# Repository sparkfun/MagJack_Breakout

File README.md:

SparkFun RJ45 MagJack Breakout
================================

[*SparkFun RJ45 MagJack Breakout(BOB-13021)*](https://www.sparkfun.com/products/13021)

This is the SparkFun RJ45 MagJack Breakout, a simple board that will provide you with a way to put an ethernet port into your breadboard. 

Repository Contents
-------------------
* **/Fritzing** - Fritzing Example wiring images
* **/Hardware** - All Eagle design files (.brd, .sch)
* **/Production** - Test bed files and production panel files

License Information
-------------------
The hardware is released under [Creative Commons ShareAlike 4.0 International](https://creativecommons.org/licenses/by-sa/4.0/).
The code is beerware; if you see me (or any other SparkFun employee) at the local, and you've found our code helpful, please buy us a round!

Distributed as-is; no warranty is given.

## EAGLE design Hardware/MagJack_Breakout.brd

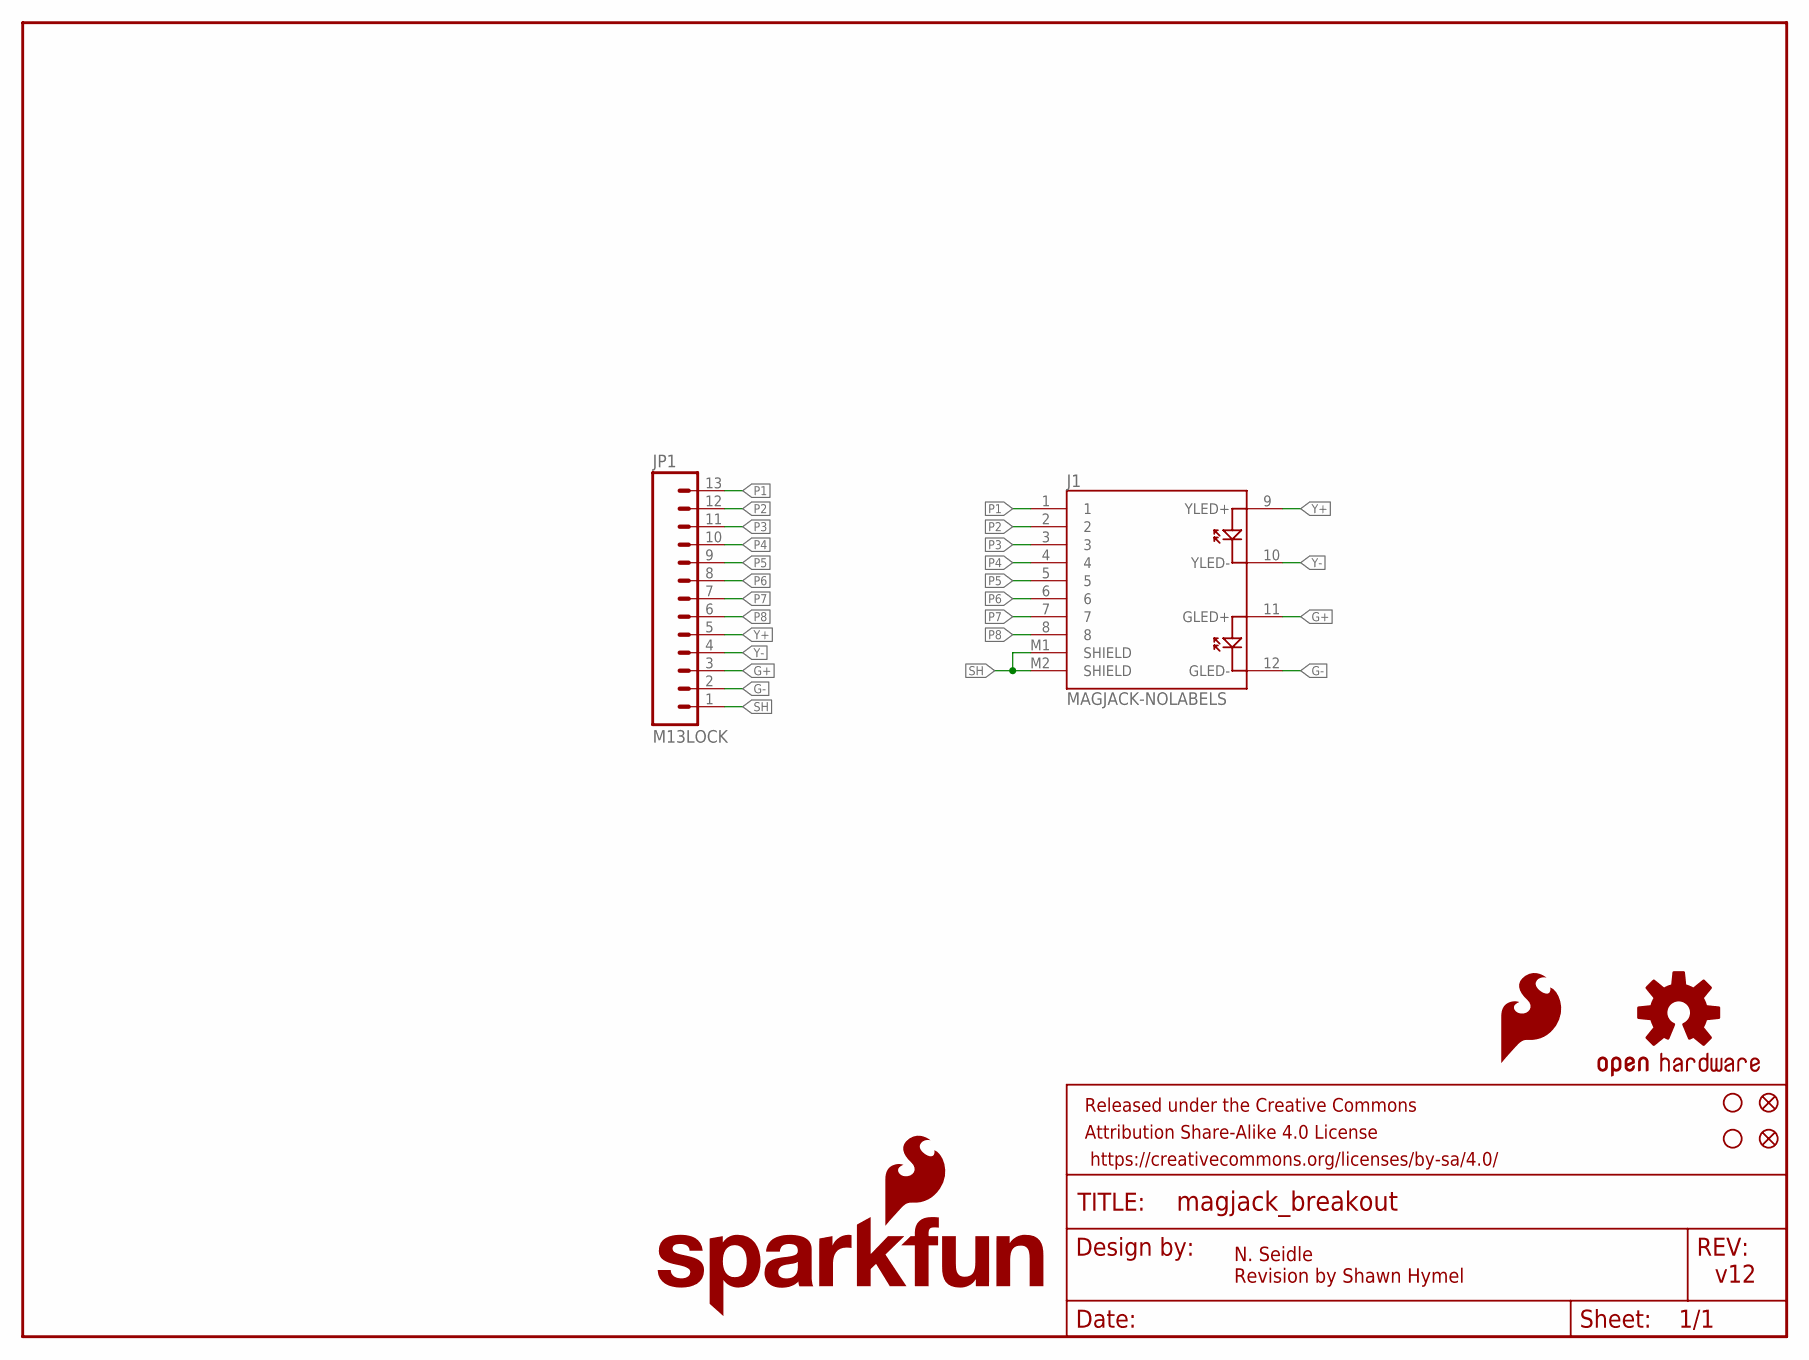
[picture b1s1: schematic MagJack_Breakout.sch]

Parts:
FID1, FID2: FIDUCIAL1X2; FIDUCIAL-1X2
FRAME1: FRAME-LETTER; CREATIVE_COMMONS
J1: MAGJACK-NOLABELS; MAGJACK
JP1: M13LOCK; 1X13_LOCK
LOGO1: OSHW-LOGOS; OSHW-LOGO-S
LOGO2: SFE_LOGO_FLAME.1_INCH; SFE_LOGO_FLAME_.1
LOGO3: SFE_LOGO_NAME_FLAME.1_INCH; SFE_LOGO_NAME_FLAME_.1
STANDOFF3, STANDOFF5: STAND-OFF

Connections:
G+: J1.11 (GLED+), JP1.3
G-: J1.12 (GLED-), JP1.2
P1: J1.1, JP1.13
P2: J1.2, JP1.12
P3: J1.3, JP1.11
P4: J1.4, JP1.10
P5: J1.5, JP1.9
P6: J1.6, JP1.8
P7: J1.7, JP1.7
P8: J1.8, JP1.6
SH: J1.M1 (SHIELD), J1.M2 (SHIELD), JP1.1
Y+: J1.9 (YLED+), JP1.5
Y-: J1.10 (YLED-), JP1.4

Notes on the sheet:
N. Seidle Revision by Shawn Hymel
v12

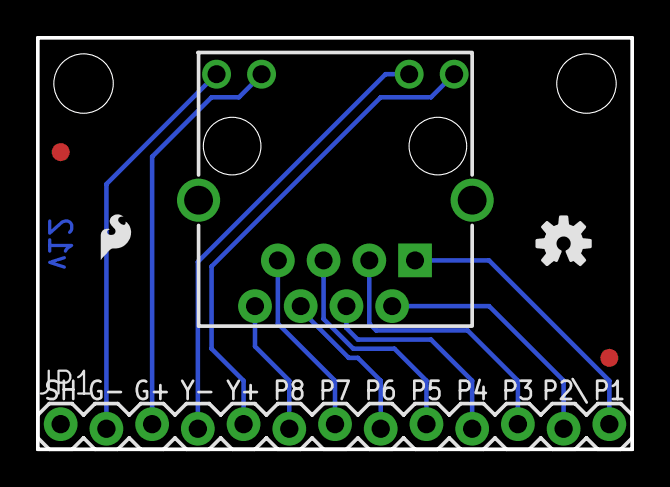
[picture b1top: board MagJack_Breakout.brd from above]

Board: 2 copper layers, 33.0 x 22.9 mm, 10 parts (1 on the bottom side), 13 nets.

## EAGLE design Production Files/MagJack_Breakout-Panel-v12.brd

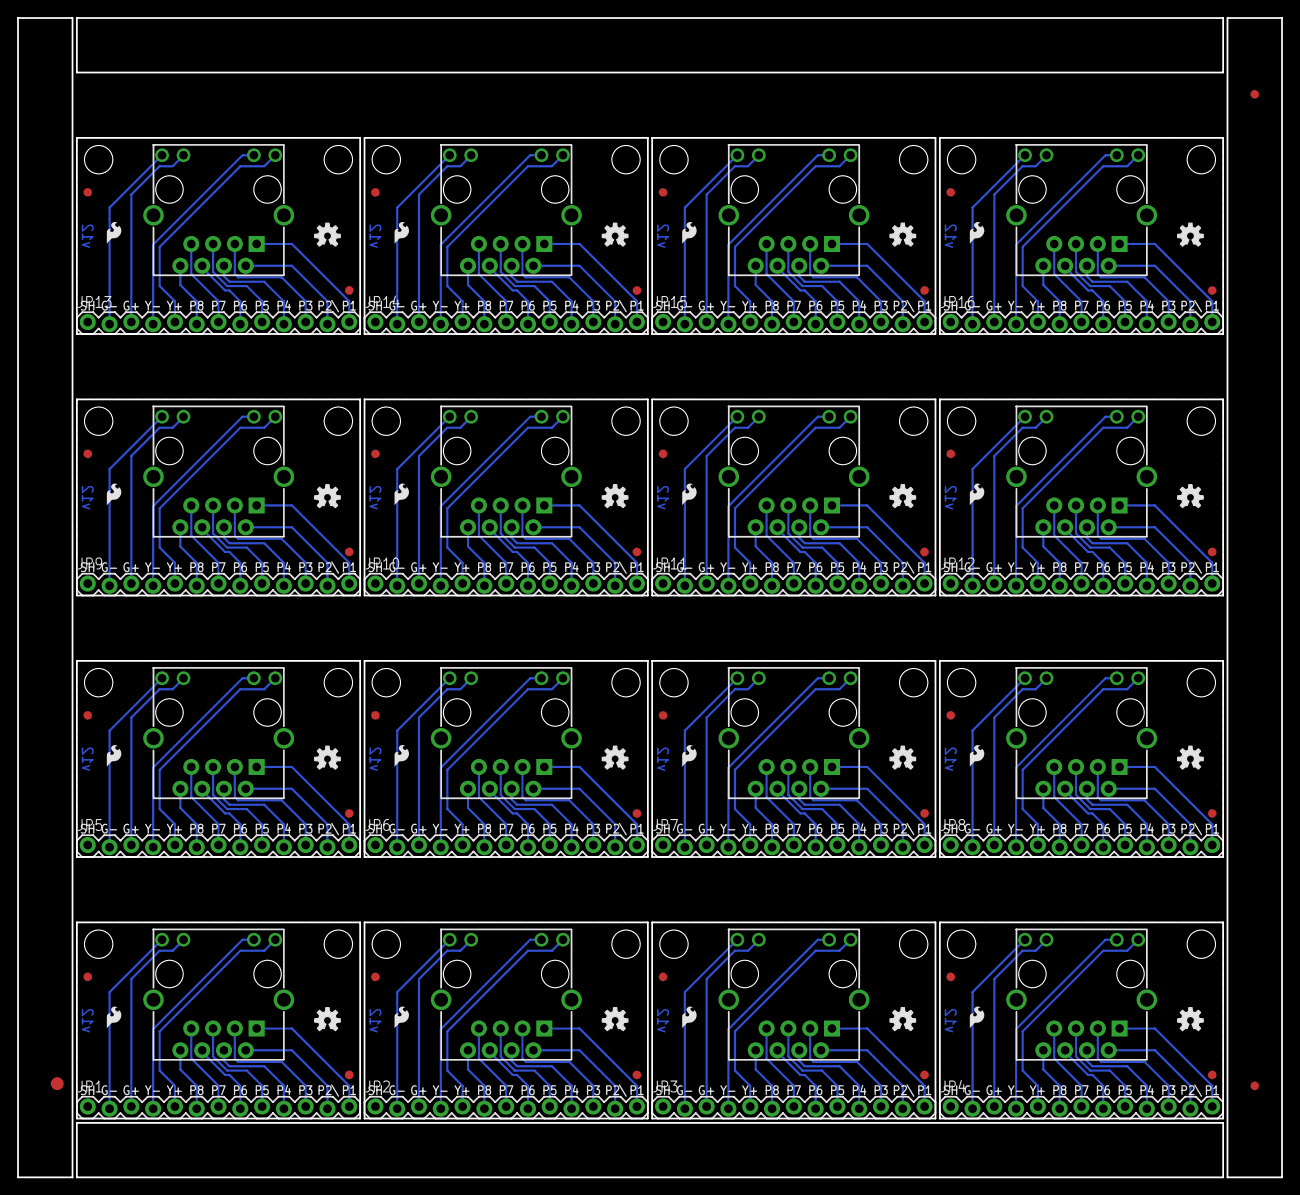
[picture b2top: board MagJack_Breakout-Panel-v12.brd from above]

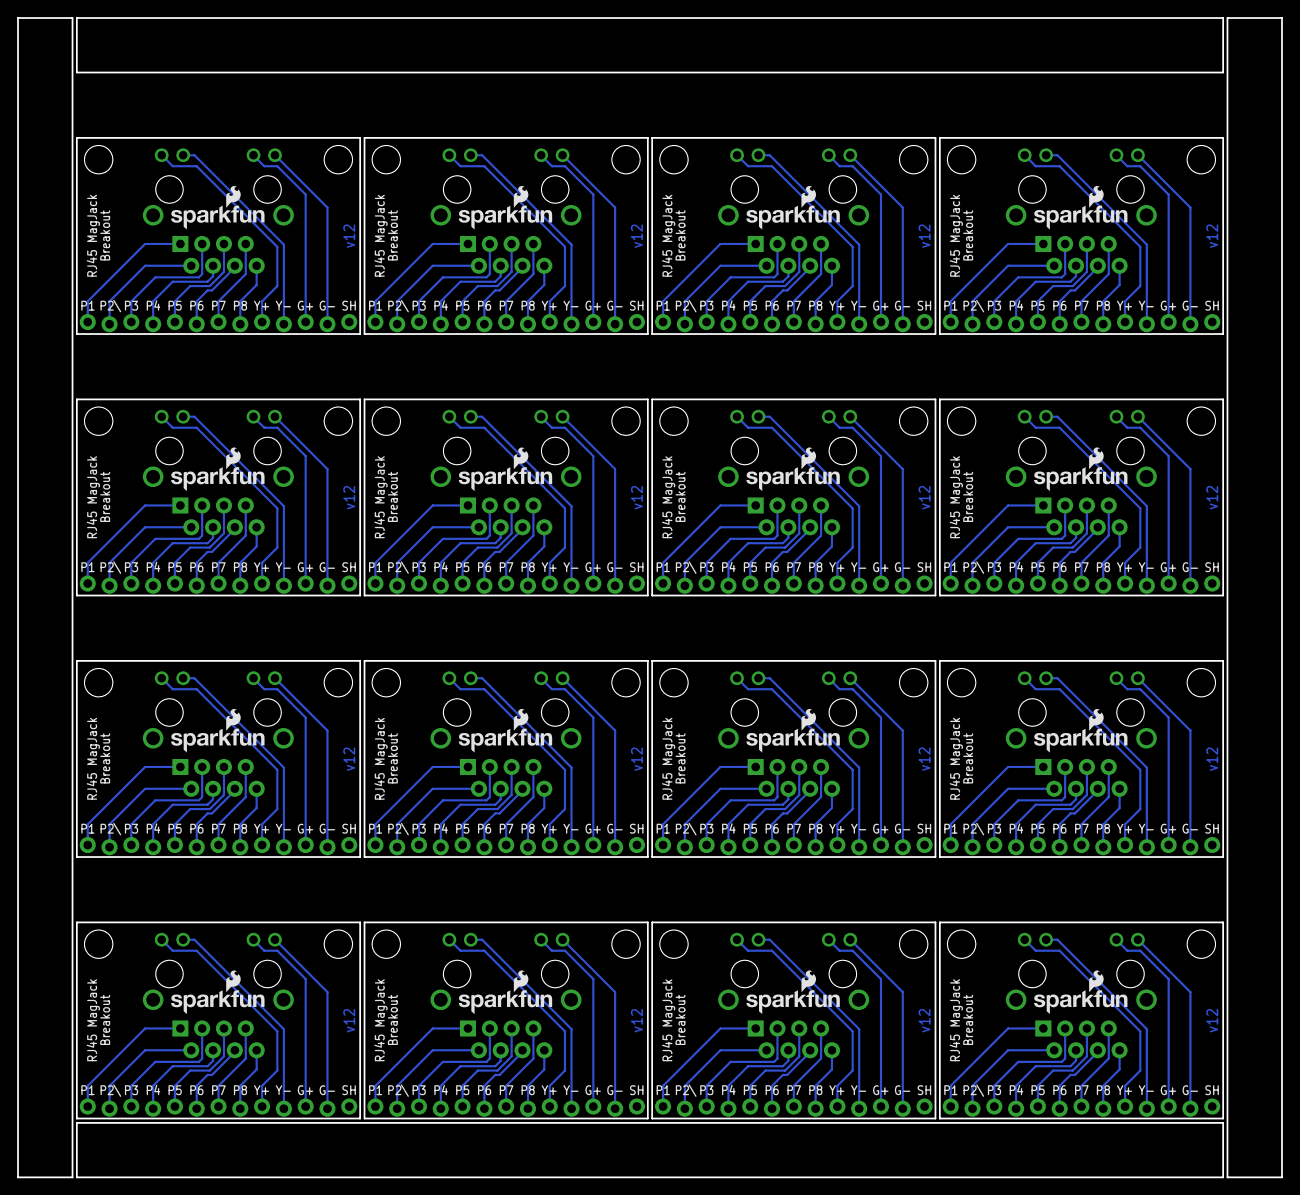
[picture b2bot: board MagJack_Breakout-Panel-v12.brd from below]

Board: 2 copper layers, 147.3 x 135.1 mm, 147 parts (16 on the bottom side), 208 nets.

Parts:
E$1: FIDUCIAL-1.5X3
E$4, E$7: FIDUCIAL-1X2
FID1, FID2, FID3, FID4, FID5, FID6, FID7, FID8, FID9, FID10, FID11, FID12, FID13, FID14, FID15, FID16, FID17, FID18, FID19, FID20, FID21, FID22, FID23, FID24, FID25, FID26, FID27, FID28, FID29, FID30, FID31, FID32: FIDUCIAL1X2; FIDUCIAL-1X2
J1, J2, J3, J4, J5, J6, J7, J8, J9, J10, J11, J12, J13, J14, J15, J16: MAGJACK-NOLABELS; MAGJACK
JP1, JP2, JP3, JP4, JP5, JP6, JP7, JP8, JP9, JP10, JP11, JP12, JP13, JP14, JP15, JP16: M13LOCK; 1X13_LOCK
LOGO1, LOGO4, LOGO7, LOGO10, LOGO13, LOGO16, LOGO19, LOGO22, LOGO25, LOGO28, LOGO31, LOGO34, LOGO37, LOGO40, LOGO43, LOGO46: OSHW-LOGOS; OSHW-LOGO-S
LOGO2, LOGO5, LOGO8, LOGO11, LOGO14, LOGO17, LOGO20, LOGO23, LOGO26, LOGO29, LOGO32, LOGO35, LOGO38, LOGO41, LOGO44, LOGO47: SFE_LOGO_FLAME.1_INCH; SFE_LOGO_FLAME_.1
LOGO3, LOGO6, LOGO9, LOGO12, LOGO15, LOGO18, LOGO21, LOGO24, LOGO27, LOGO30, LOGO33, LOGO36, LOGO39, LOGO42, LOGO45, LOGO48: SFE_LOGO_NAME_FLAME.1_INCH; SFE_LOGO_NAME_FLAME_.1
STANDOFF1, STANDOFF2, STANDOFF3, STANDOFF4, STANDOFF5, STANDOFF6, STANDOFF7, STANDOFF8, STANDOFF9, STANDOFF10, STANDOFF11, STANDOFF12, STANDOFF13, STANDOFF14, STANDOFF15, STANDOFF16, STANDOFF17, STANDOFF18, STANDOFF19, STANDOFF20, STANDOFF21, STANDOFF22, STANDOFF23, STANDOFF24, STANDOFF25, STANDOFF26, STANDOFF27, STANDOFF28, STANDOFF29, STANDOFF30, STANDOFF31, STANDOFF32: STAND-OFF

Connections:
G+: J1.11, JP1.3
G+1: J2.11, JP2.3
G+2: J3.11, JP3.3
G+3: J4.11, JP4.3
G+4: J5.11, JP5.3
G+5: J6.11, JP6.3
G+6: J7.11, JP7.3
G+7: J8.11, JP8.3
G+8: J9.11, JP9.3
G+9: J10.11, JP10.3
G+10: J11.11, JP11.3
G+11: J12.11, JP12.3
G+12: J13.11, JP13.3
G+13: J14.11, JP14.3
G+14: J15.11, JP15.3
G+15: J16.11, JP16.3
G-: J1.12, JP1.2
G-1: J2.12, JP2.2
G-2: J3.12, JP3.2
G-3: J4.12, JP4.2
G-4: J5.12, JP5.2
G-5: J6.12, JP6.2
G-6: J7.12, JP7.2
G-7: J8.12, JP8.2
G-8: J9.12, JP9.2
G-9: J10.12, JP10.2
G-10: J11.12, JP11.2
G-11: J12.12, JP12.2
G-12: J13.12, JP13.2
G-13: J14.12, JP14.2
G-14: J15.12, JP15.2
G-15: J16.12, JP16.2
P1: J1.1, JP1.13
P2: J1.2, JP1.12
P3: J1.3, JP1.11
P4: J1.4, JP1.10
P5: J1.5, JP1.9
P6: J1.6, JP1.8
P7: J1.7, JP1.7
P8: J1.8, JP1.6
P9: J2.1, JP2.13
P10: J2.2, JP2.12
P11: J2.3, JP2.11
P12: J2.4, JP2.10
P13: J2.5, JP2.9
P14: J2.6, JP2.8
P15: J2.7, JP2.7
P16: J2.8, JP2.6
P17: J3.1, JP3.13
P18: J3.2, JP3.12
P19: J3.3, JP3.11
P20: J3.4, JP3.10
P21: J3.5, JP3.9
P22: J3.6, JP3.8
P23: J3.7, JP3.7
P24: J3.8, JP3.6
P25: J4.1, JP4.13
P26: J4.2, JP4.12
P27: J4.3, JP4.11
P28: J4.4, JP4.10
P29: J4.5, JP4.9
P30: J4.6, JP4.8
P31: J4.7, JP4.7
P32: J4.8, JP4.6
P33: J5.1, JP5.13
P34: J5.2, JP5.12
P35: J5.3, JP5.11
P36: J5.4, JP5.10
P37: J5.5, JP5.9
P38: J5.6, JP5.8
P39: J5.7, JP5.7
P40: J5.8, JP5.6
P41: J6.1, JP6.13
P42: J6.2, JP6.12
P43: J6.3, JP6.11
P44: J6.4, JP6.10
P45: J6.5, JP6.9
P46: J6.6, JP6.8
P47: J6.7, JP6.7
P48: J6.8, JP6.6
P49: J7.1, JP7.13
P50: J7.2, JP7.12
P51: J7.3, JP7.11
P52: J7.4, JP7.10
P53: J7.5, JP7.9
P54: J7.6, JP7.8
P55: J7.7, JP7.7
P56: J7.8, JP7.6
P57: J8.1, JP8.13
P58: J8.2, JP8.12
P59: J8.3, JP8.11
P60: J8.4, JP8.10
P61: J8.5, JP8.9
P62: J8.6, JP8.8
P63: J8.7, JP8.7
P64: J8.8, JP8.6
P65: J9.1, JP9.13
P66: J9.2, JP9.12
P67: J9.3, JP9.11
P68: J9.4, JP9.10
P69: J9.5, JP9.9
P70: J9.6, JP9.8
P71: J9.7, JP9.7
P72: J9.8, JP9.6
P73: J10.1, JP10.13
P74: J10.2, JP10.12
P75: J10.3, JP10.11
P76: J10.4, JP10.10
P77: J10.5, JP10.9
P78: J10.6, JP10.8
P79: J10.7, JP10.7
P80: J10.8, JP10.6
P81: J11.1, JP11.13
P82: J11.2, JP11.12
P83: J11.3, JP11.11
P84: J11.4, JP11.10
P85: J11.5, JP11.9
P86: J11.6, JP11.8
P87: J11.7, JP11.7
P88: J11.8, JP11.6
P89: J12.1, JP12.13
P90: J12.2, JP12.12
P91: J12.3, JP12.11
P92: J12.4, JP12.10
P93: J12.5, JP12.9
P94: J12.6, JP12.8
P95: J12.7, JP12.7
P96: J12.8, JP12.6
P97: J13.1, JP13.13
P98: J13.2, JP13.12
P99: J13.3, JP13.11
P100: J13.4, JP13.10
P101: J13.5, JP13.9
P102: J13.6, JP13.8
P103: J13.7, JP13.7
P104: J13.8, JP13.6
P105: J14.1, JP14.13
P106: J14.2, JP14.12
P107: J14.3, JP14.11
P108: J14.4, JP14.10
P109: J14.5, JP14.9
P110: J14.6, JP14.8
P111: J14.7, JP14.7
P112: J14.8, JP14.6
P113: J15.1, JP15.13
P114: J15.2, JP15.12
P115: J15.3, JP15.11
P116: J15.4, JP15.10
P117: J15.5, JP15.9
P118: J15.6, JP15.8
P119: J15.7, JP15.7
P120: J15.8, JP15.6
P121: J16.1, JP16.13
P122: J16.2, JP16.12
P123: J16.3, JP16.11
P124: J16.4, JP16.10
P125: J16.5, JP16.9
P126: J16.6, JP16.8
P127: J16.7, JP16.7
P128: J16.8, JP16.6
SH: J1.M1, J1.M2, JP1.1
SH1: J2.M1, J2.M2, JP2.1
SH2: J3.M1, J3.M2, JP3.1
SH3: J4.M1, J4.M2, JP4.1
SH4: J5.M1, J5.M2, JP5.1
SH5: J6.M1, J6.M2, JP6.1
SH6: J7.M1, J7.M2, JP7.1
SH7: J8.M1, J8.M2, JP8.1
SH8: J9.M1, J9.M2, JP9.1
SH9: J10.M1, J10.M2, JP10.1
SH10: J11.M1, J11.M2, JP11.1
SH11: J12.M1, J12.M2, JP12.1
SH12: J13.M1, J13.M2, JP13.1
SH13: J14.M1, J14.M2, JP14.1
SH14: J15.M1, J15.M2, JP15.1
SH15: J16.M1, J16.M2, JP16.1
Y+: J1.9, JP1.5
Y+1: J2.9, JP2.5
Y+2: J3.9, JP3.5
Y+3: J4.9, JP4.5
Y+4: J5.9, JP5.5
Y+5: J6.9, JP6.5
Y+6: J7.9, JP7.5
Y+7: J8.9, JP8.5
Y+8: J9.9, JP9.5
Y+9: J10.9, JP10.5
Y+10: J11.9, JP11.5
Y+11: J12.9, JP12.5
Y+12: J13.9, JP13.5
Y+13: J14.9, JP14.5
Y+14: J15.9, JP15.5
Y+15: J16.9, JP16.5
Y-: J1.10, JP1.4
Y-1: J2.10, JP2.4
Y-2: J3.10, JP3.4
Y-3: J4.10, JP4.4
Y-4: J5.10, JP5.4
Y-5: J6.10, JP6.4
Y-6: J7.10, JP7.4
Y-7: J8.10, JP8.4
Y-8: J9.10, JP9.4
Y-9: J10.10, JP10.4
Y-10: J11.10, JP11.4
Y-11: J12.10, JP12.4
Y-12: J13.10, JP13.4
Y-13: J14.10, JP14.4
Y-14: J15.10, JP15.4
Y-15: J16.10, JP16.4

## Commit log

2014-05-27 Created initial schematic
2014-05-28 Completed revised layout for prototypes
2014-05-28 Added Nate as original designer
2014-06-18 Added Fritzing diagrams
2014-06-18 Moved bottom/header section down by 0.1 in,
2014-06-25 Changed shield trace to top-side pour
2014-06-25 Added locking header
2014-06-26 created panel v12
2015-02-13 Updating directory names, adding product info to README

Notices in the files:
parts and their libraries:
SparkFun-Aesthetics: Licensing: Creative Commons ShareAlike 4.0 International - https://creativecommons.org/licenses/by-sa/4.0
SparkFun-Aesthetics: Released under the Creative Commons Attribution Share-Alike 4.0 License
SparkFun-Aesthetics: Released under the Creative Commons
